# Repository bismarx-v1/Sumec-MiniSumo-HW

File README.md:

# SUMEC - HARDWARE - ELECTRONICS

**SUMEC** - is an autonomous MiniSumo robot, that is designed to compete in MiniSumo competitions. MiniSumo robots are small 100mmx100mm autonomous robots that combine electronics, software and mechanics into one project, their task it to push their opponent out of a ring. This project is led and managed by [SPŠ na Proseku](https://www.sps-prosek.cz) students.

## Table of Contents
- Description
- Contents
- Contributors
- Our Suppliers
- Contact
- Acknowledgements

## Description
This GitHub repository contains PCB files, gerber plots and main electronics used by SUMEC MiniSumo robot.

## Contents
- **main_hw**: Includes schematics and PCB files for the main board, production files such as Gerber plots and BOMs, .step files of the board, and PDF plots.
- **libs**: Contains needed libraries such as the footprint folder, 3D files in .step format, and the symbol library for schematics.

## Contributors
**HARDWARE Repository Supervisor**:
- **Savva Popov** - Head Hardware Developer and PCB Designer

**Project Contributors**:
- **Antonín Havlík** - Head Software Developer
- **Šimon Šťastný** - Head Mechanical Designer and Developer
- **Jonáš Jarý** - Mechanical Developer, Software and Hardware Development Assistant
- **Lukáš Houdek** - Mechanical Designer and Developer, 3D Printing Expert
- **Roselyn Natani Šimáčková** - Software developer, head functions developer

## Our Suppliers
We buy our components from:
- Mouser Electronics
- GM Electronics
- TME
- BotLand

## Contact
If you have any questions, suggestions, or issues regarding this project or repository, please feel free to contact:

### **Savva Popov** - Head Hardware Developer
  - Email: savva.popov.sp@gmail.com
  - LinkedIn: [Savva Popov](https://www.linkedin.com/in/savva-popov/)

### Other Contacts:
- **Antonín Havlík** - Head Software Developer
  - Email: [HAVLIK EMAIL]
- **Šimon Šťastný** - Head Mechanical Designer and Developer
  - Email: simon.ststn@gmail.com
- **Jonáš Jarý** - Mechanical Developer, Software and Hardware Development Assistant
  - Email: jary.jonas@gmail.com
- **Lukáš Houdek** - Mechanical Designer and Developer, 3D Printing Expert
  - Email: [HOUDEK EMAIL]
- **Roselyn Natani Šimáčková** - Software Developer, Head functions developer
  - Email: [SIMACKOVA EMAIL]

## Acknowledgements
We would like to thank Ing. Jaroslav Bušek PhD, for providing contacts and mentoring during the development of this project, and our school SPŠ na Proseku for providing workplace, knowledge, and top-notch equipment.

**Sending love from the Czech Republic!**

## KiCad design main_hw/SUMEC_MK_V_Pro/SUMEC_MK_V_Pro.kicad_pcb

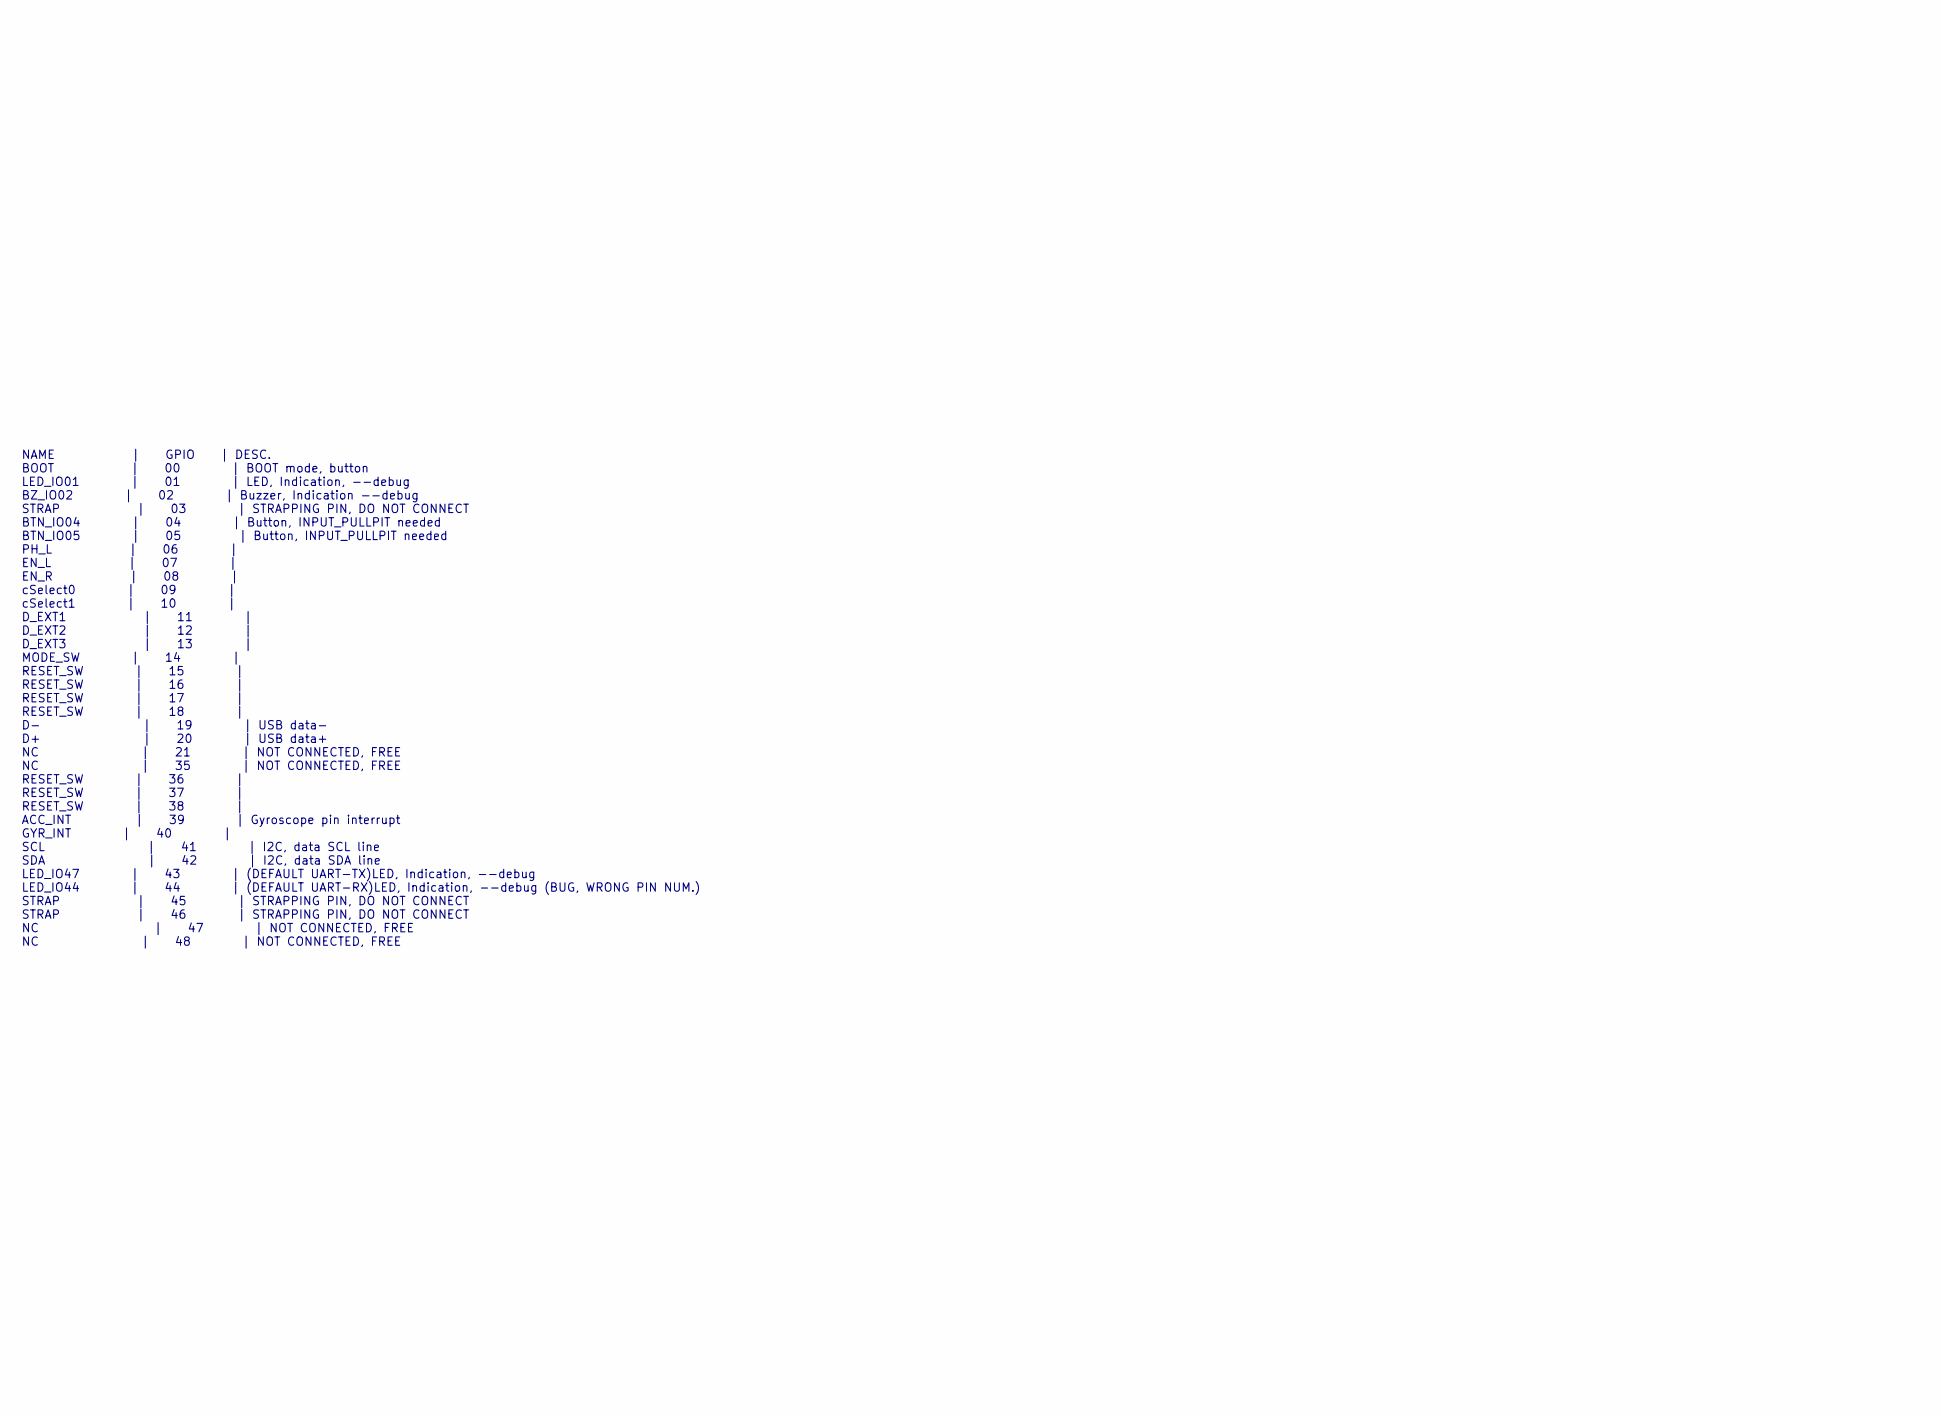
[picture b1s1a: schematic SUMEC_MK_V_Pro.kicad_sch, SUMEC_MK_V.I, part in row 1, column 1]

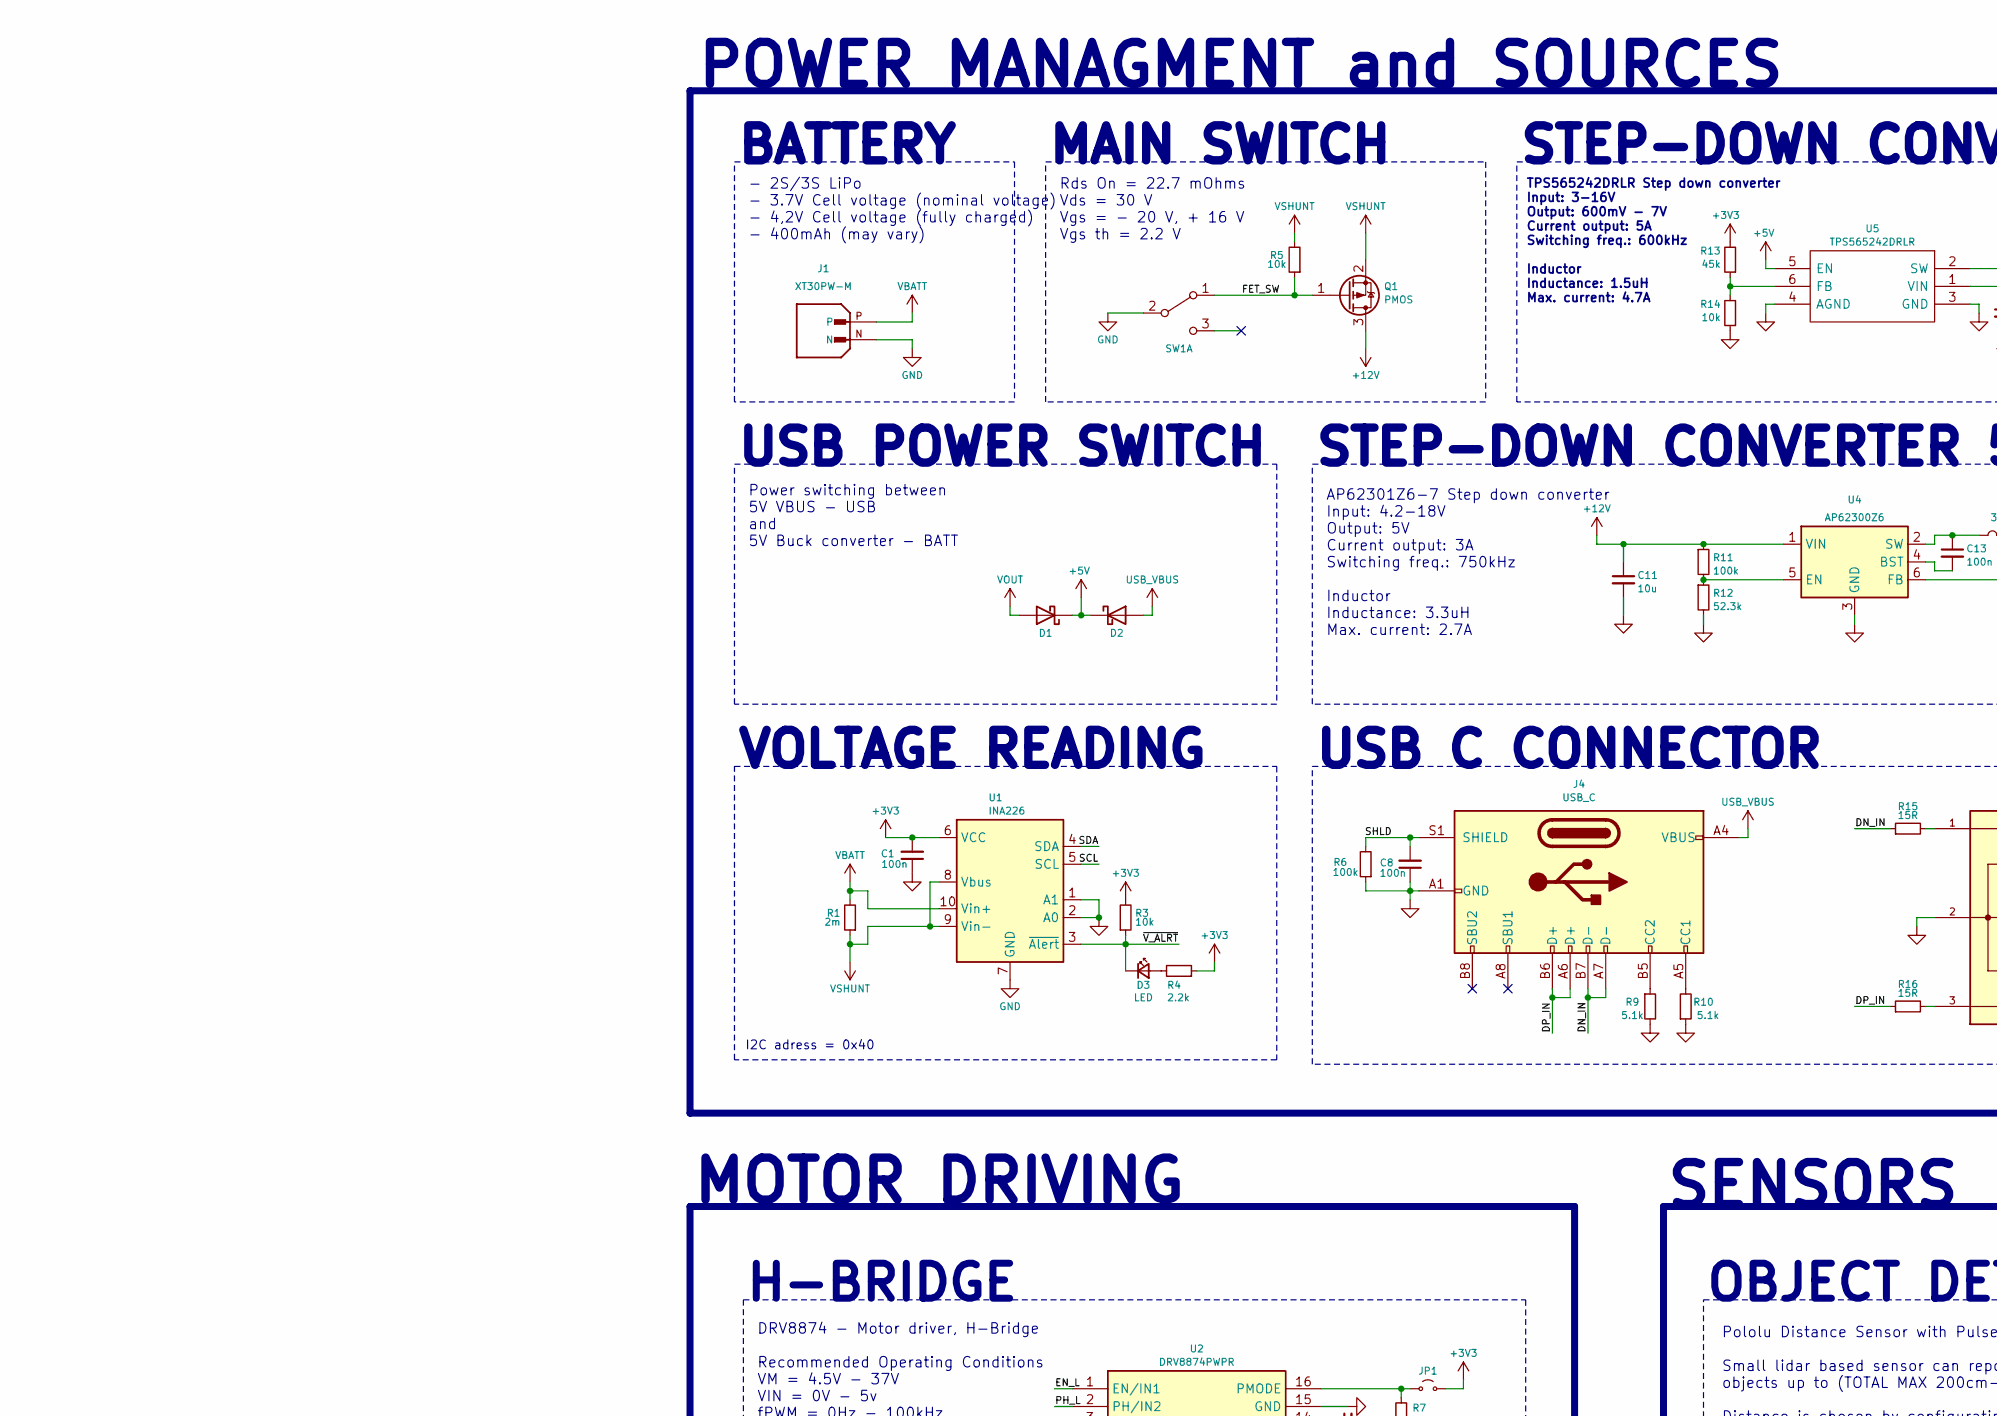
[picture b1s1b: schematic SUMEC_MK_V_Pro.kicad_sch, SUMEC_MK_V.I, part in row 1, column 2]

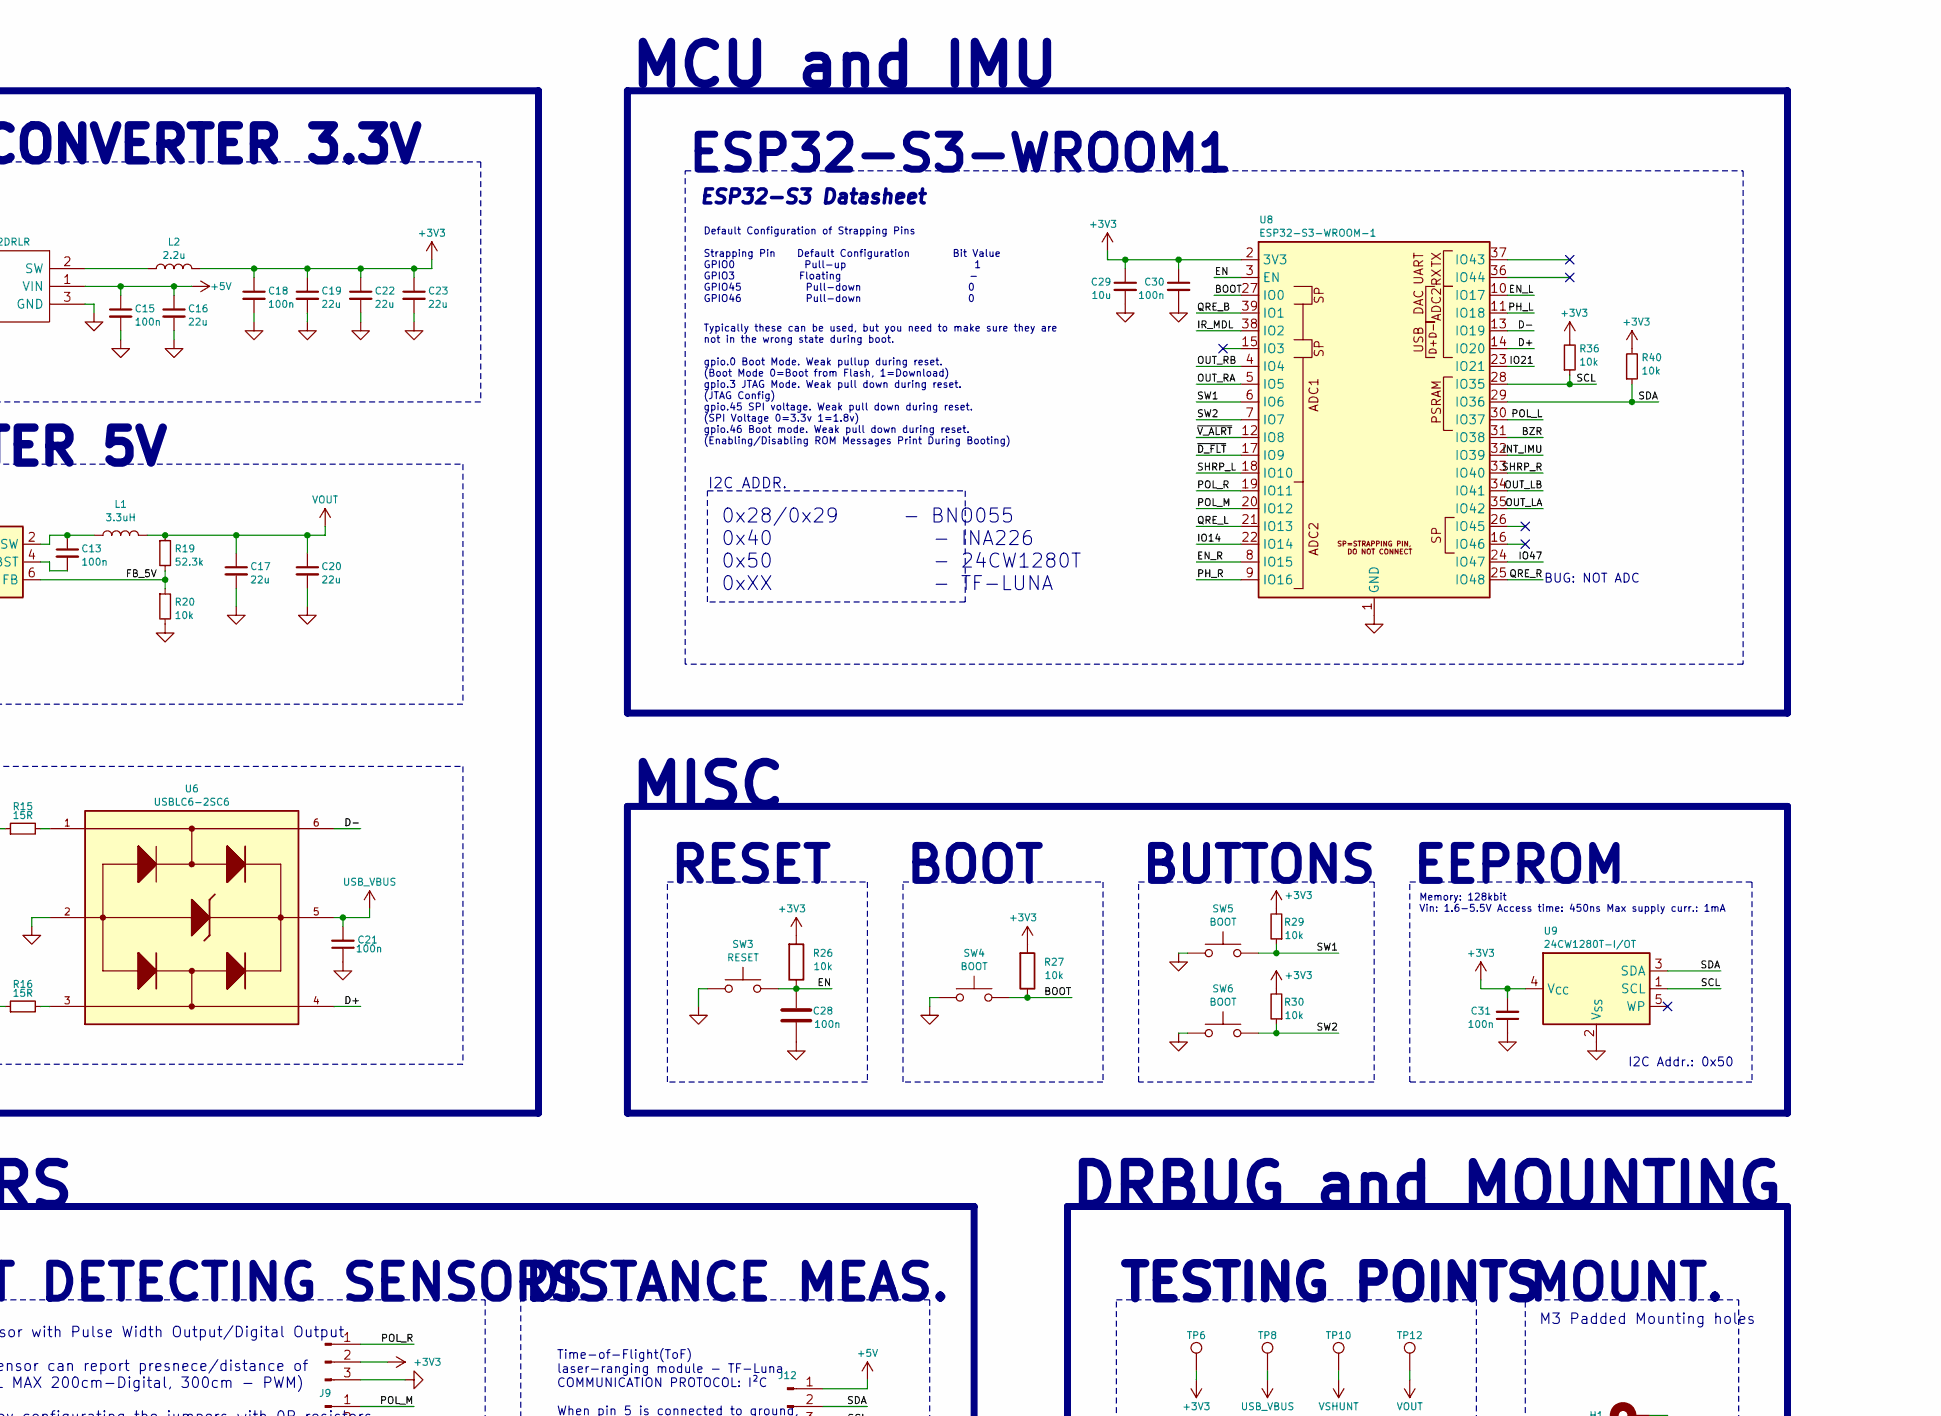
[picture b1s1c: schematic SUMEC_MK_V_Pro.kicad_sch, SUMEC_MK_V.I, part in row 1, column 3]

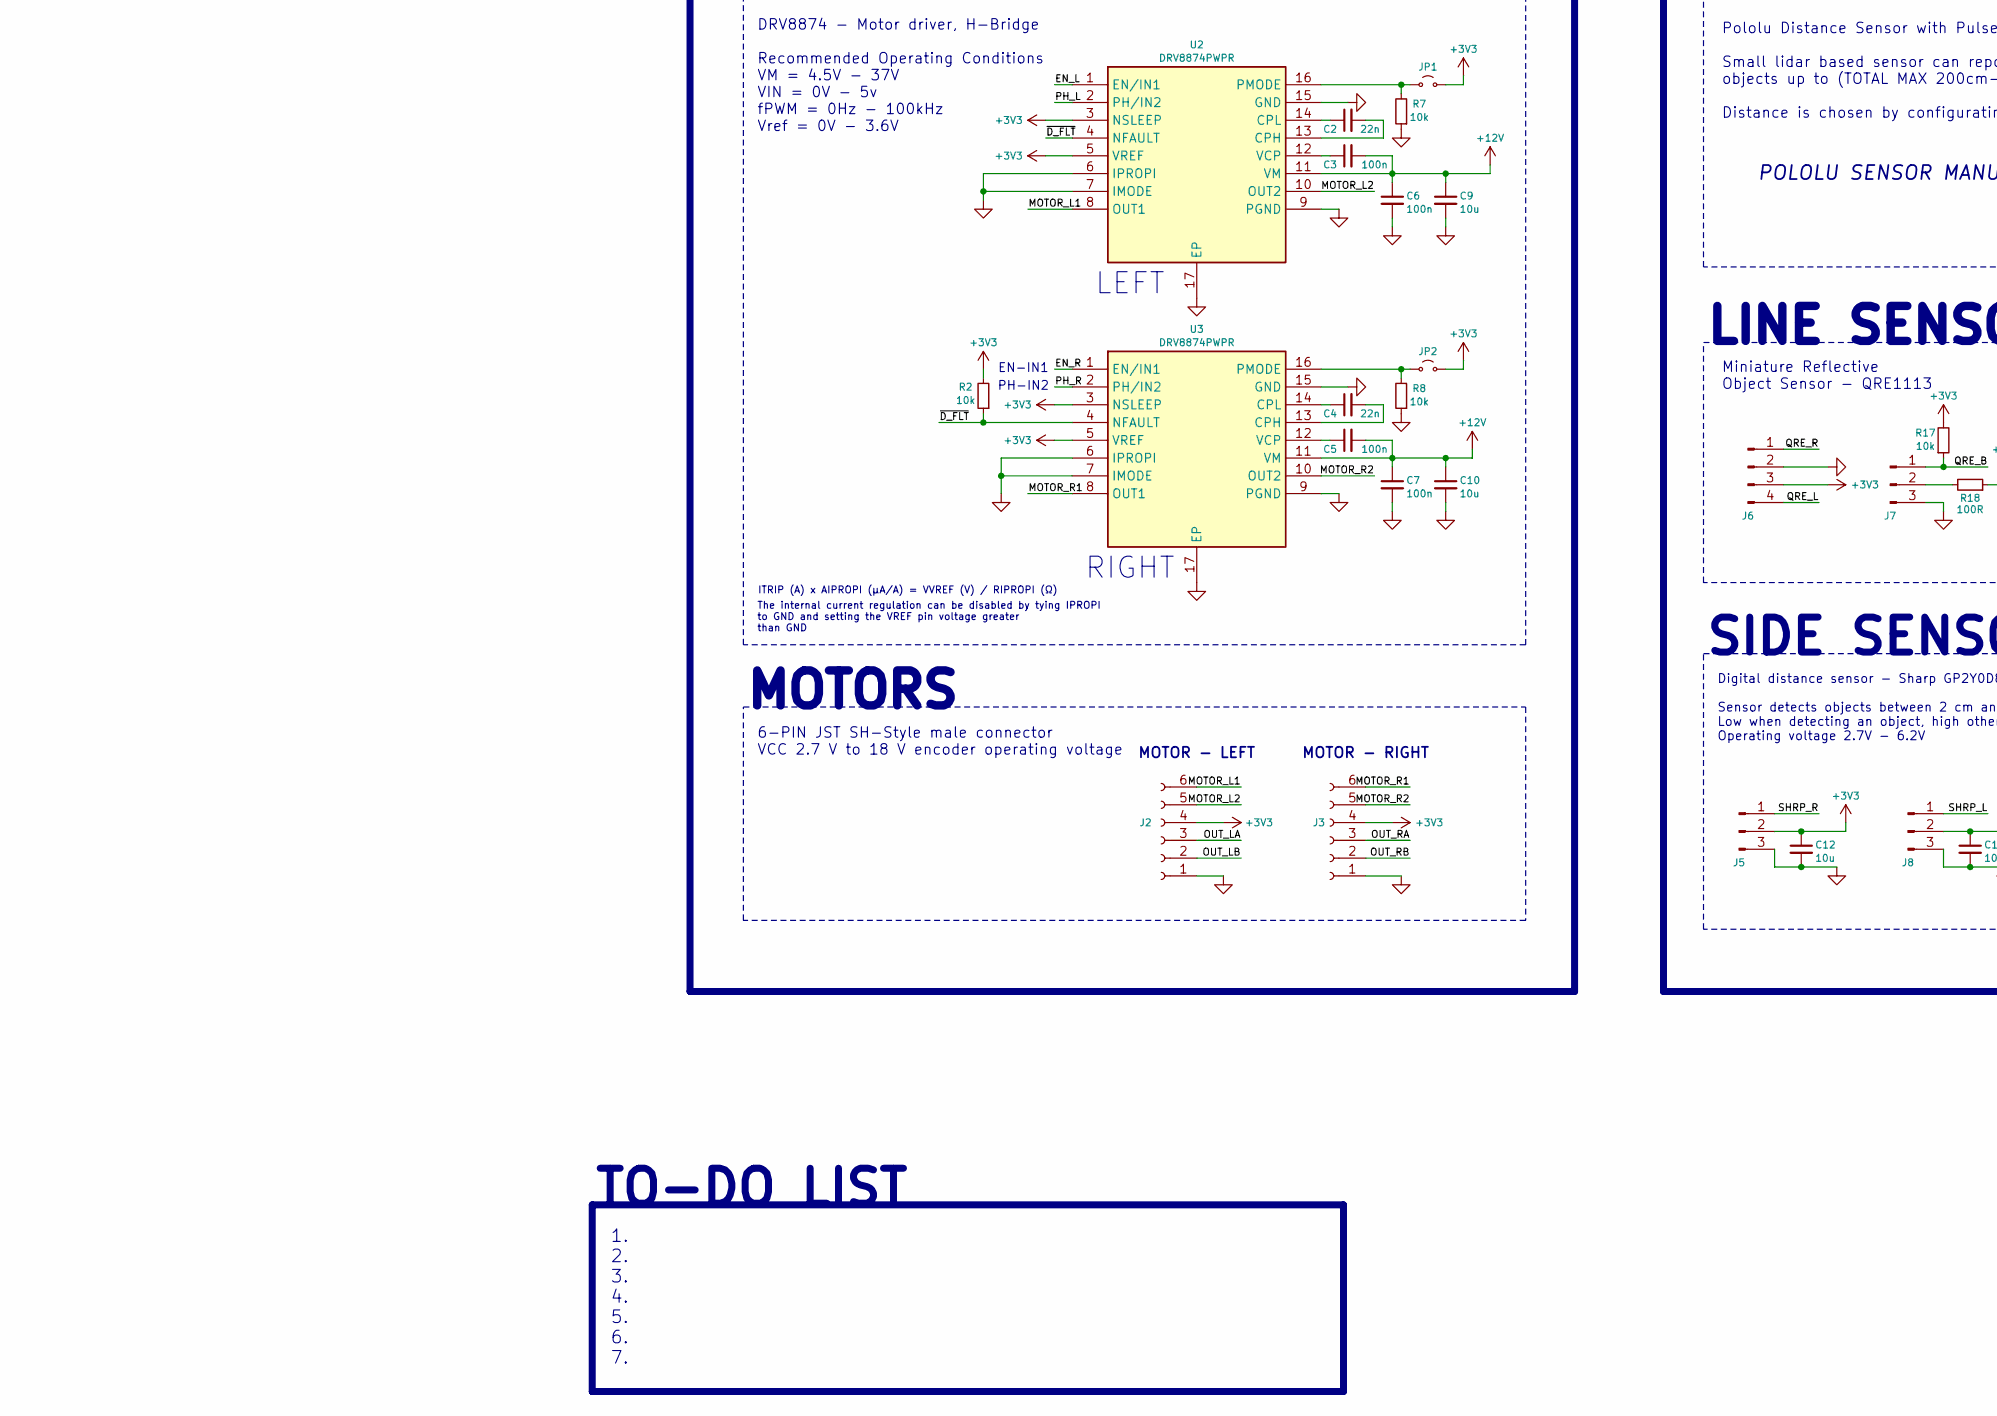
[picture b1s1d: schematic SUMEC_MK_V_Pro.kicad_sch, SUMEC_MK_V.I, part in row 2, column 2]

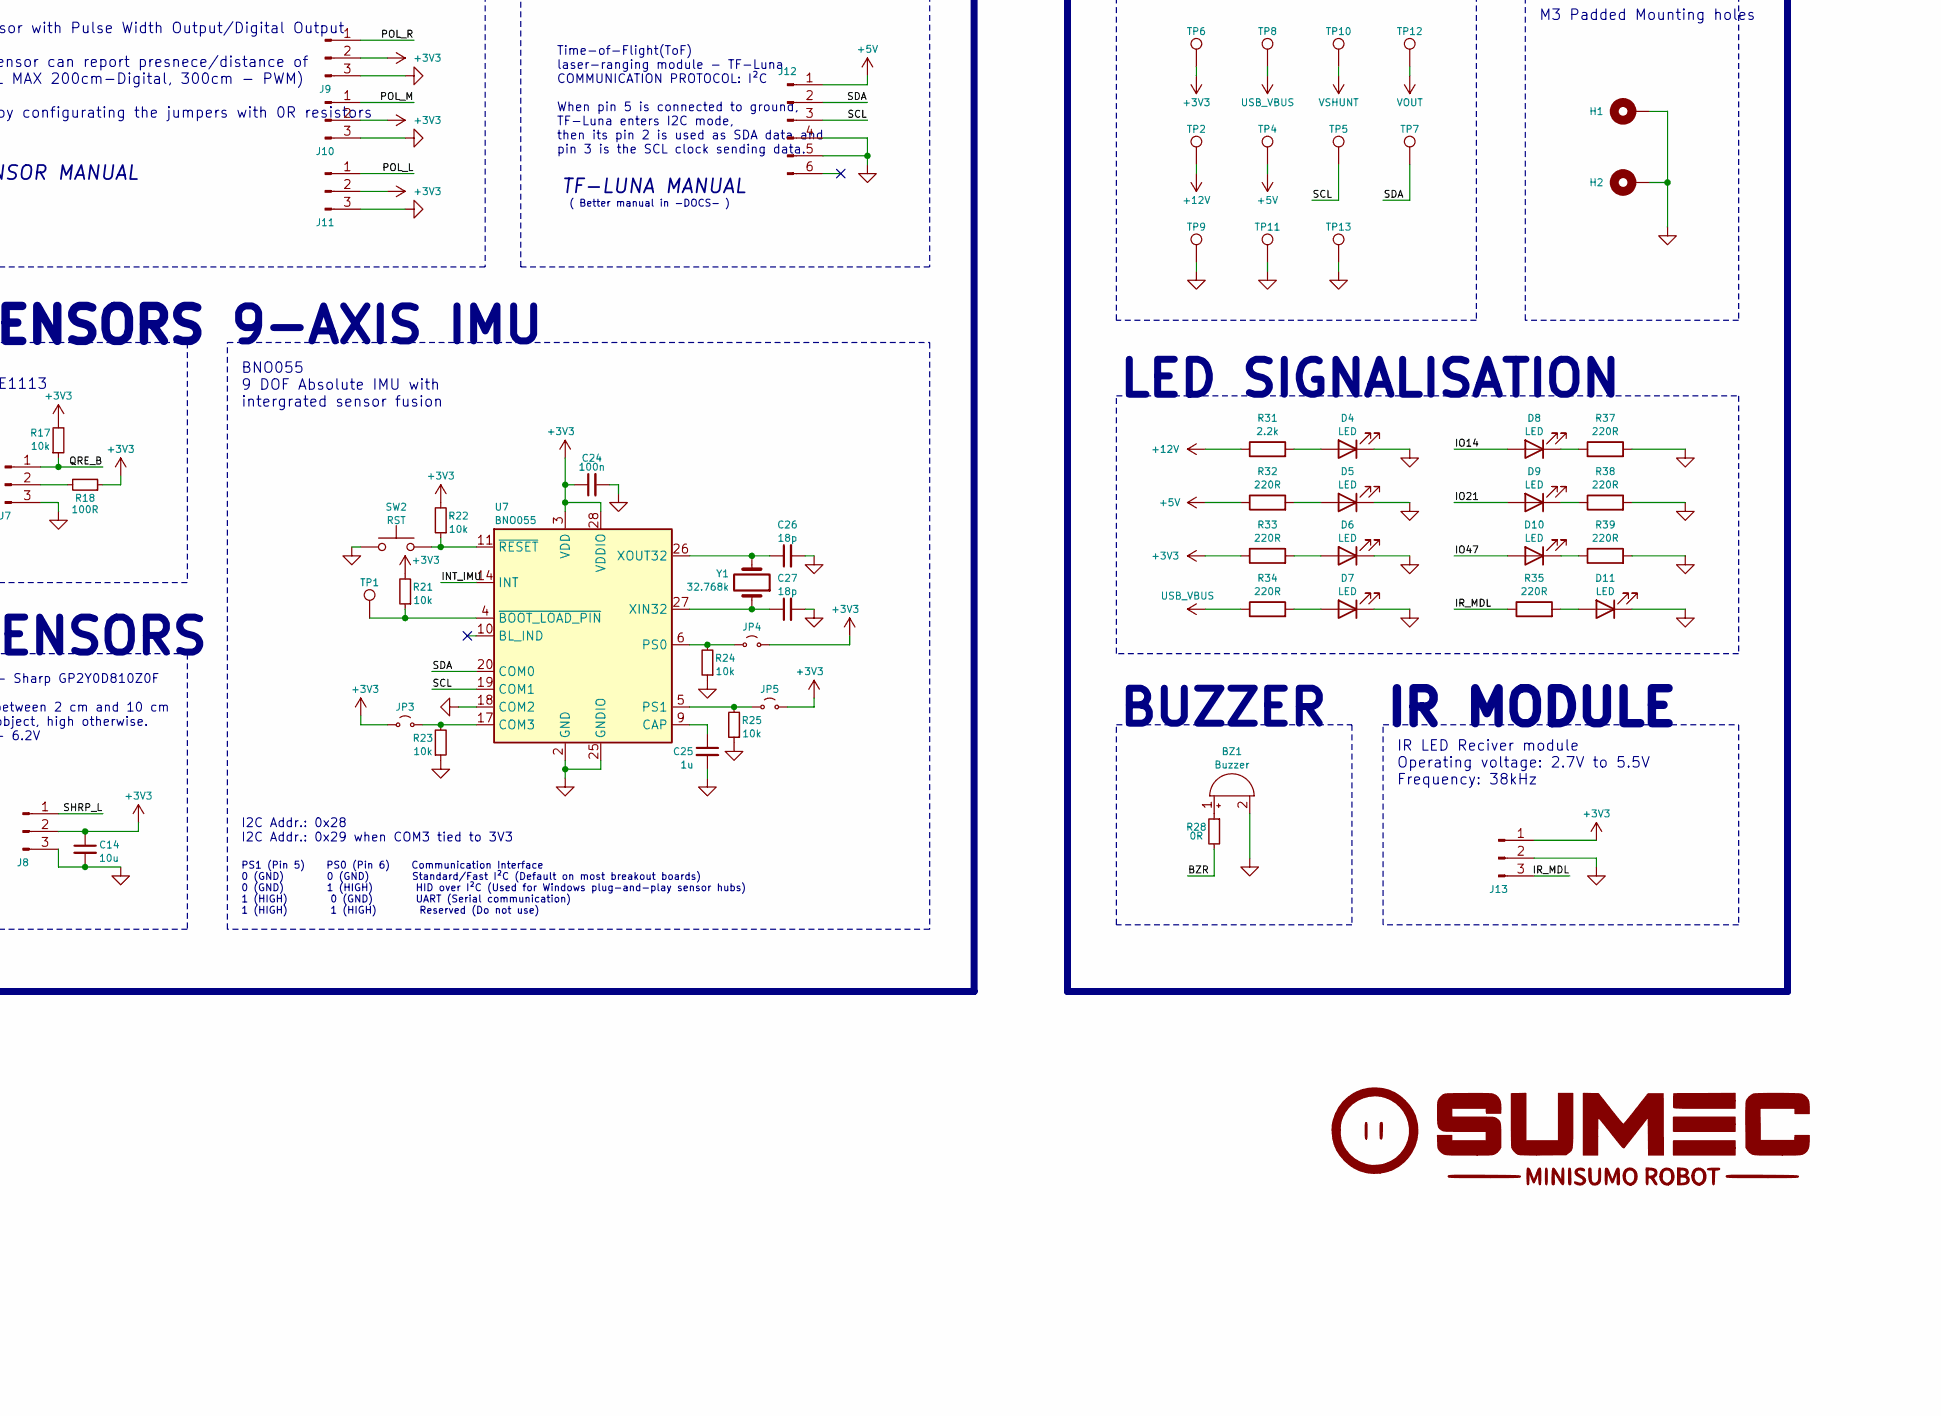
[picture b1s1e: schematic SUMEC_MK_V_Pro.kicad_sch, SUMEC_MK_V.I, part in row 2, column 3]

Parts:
BZ1: Buzzer; BUZZER_CUI_CPT
C1, C3, C5, C6, C7, C8, C13, C15, C18, C21, C24, C28, C30, C31: 100n; C_0805_2012Metric
C2, C4: 22n; C_0805_2012Metric
C9, C10, C11, C12, C14, C29: 10u; C_0805_2012Metric
C16, C17, C19, C20, C22, C23: 22u; C_0805_2012Metric
C25: 1u; C_0805_2012Metric
C26, C27: 18p; C_0805_2012Metric
D1, D2: D_Schottky; D_1206_3216Metric
D3, D4, D5, D6, D7, D8, D9, D10, D11: LED; LED_0805_2012Metric
H1, H2: Mounting Hole M3; MountingHole_3.2mm_M3_Pad_Via
J1: XT30PW-M; PARTREV 1.2
J2, J3: Conn_01x06_Socket; JST_SH_BM06B-SRSS-TB_1x06-1MP_P1.00mm_Vertical
J4: USB_C; USB_C_Receptacle_GCT_USB4105-xx-A_16P_TopMnt_Horizontal
J5, J7, J8, J9, J10, J11: Conn_01x03_Pin; Molex_PicoBlade_53398-0371_1x03-1MP_P1.25mm_Vertical
J6: Conn_01x04_Pin; Molex_PicoBlade_53398-0471_1x04-1MP_P1.25mm_Vertical
J12: Conn_01x06_Pin; Molex_PicoBlade_53398-0671_1x06-1MP_P1.25mm_Vertical
J13: Conn_01x03_Pin; TerminalBlock_Phoenix_MPT-0,5-3-2.54_1x03_P2.54mm_Horizontal
JP1, JP2, JP3, JP4, JP5: Jumper_2_Small_Open; SolderJumper-2_P1.3mm_Open_RoundedPad1.0x1.5mm
L1: 3.3uH; L_Vishay_IHLP-1616
L2: 2.2u; L_Vishay_IHLP-1212
Q1: PMOS; SOT-23-3
R1: 2m; R_0805_2012Metric
R2, R3, R5, R7, R8, R14, R17, R20, R21, R22, R23, R24, R25, R26, R27, R29, R30, R36, R40: 10k; R_0805_2012Metric
R4, R31: 2.2k; R_0805_2012Metric
R6, R11: 100k; R_0805_2012Metric
R9, R10: 5.1k; R_0805_2012Metric
R12, R19: 52.3k; R_0805_2012Metric
R13: 45k; R_0805_2012Metric
R15, R16: 15R; R_0805_2012Metric
R18: 100R; R_0805_2012Metric
R28: 0R; R_0805_2012Metric
R32, R33, R34, R35, R37, R38, R39: 220R; R_0805_2012Metric
SW1: SW_DPDT_x2; Custom_SPDT_2.5_Switch
SW2: RST; SW_SPST_EVQPE1
SW3: RESET; SW_SPST_EVQPE1
SW4, SW5, SW6: BOOT; SW_SPST_EVQPE1
TP1, TP2, TP4, TP5, TP6, TP7, TP8, TP9, TP10, TP11, TP12, TP13: TestPoint; TestPoint_Pad_D1.5mm
U1: INA226; HVSSOP-10-1EP_3x3mm_P0.5mm_EP1.83x1.89mm
U2, U3: DRV8874PWPR; DRV8874; Manufacturer_Part_Number DRV8874PWPR; Mouser Part Number 595-DRV8874PWPR
U4: AP62300Z6; SOT-563
U5: TPS565242DRLR; SOT-563; Manufacturer_Part_Number TPS565242DRLR; Mouser Part Number 595-TPS565242DRLR
U6: USBLC6-2SC6; TSOT-23-6
U7: BNO055; LGA-28_5.2x3.8mm_P0.5mm
U8: ESP32-S3-WROOM-1
U9: 24CW1280T-I/OT; SOT-23-5
Y1: 32.768k; CM8V32768TA020125

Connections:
+3V3: C1.2, C12.1, C14.1, C18.1, C19.1, C22.1, C23.1, C24.1, C29.1, C30.1, C31.2, J2.4, J3.4, J5.2, J6.3, J8.2, J9.2, J10.2, J11.2, J13.1, JP1.2 (B), JP2.2 (B), JP3.2 (B), JP4.2 (B), JP5.2 (B), L2.2, R2.2, R3.2, R4.1, R13.2, R17.2, R18.1, R21.2, R22.2, R26.2, R27.2, R29.2, R30.2, R33.1, R36.2, R40.2, TP6.1 (1_1), U1.6 (VCC), U2.3 (NSLEEP), U2.5 (VREF), U3.3 (NSLEEP), U3.5 (VREF), U7.3 (VDD), U7.28 (VDDIO), U8.2 (3V3), U9.4 (V_{CC})
+5V: C15.1, C16.1, D1.1 (K), D2.1 (K), J12.1, R32.1, TP4.1 (1_1), U5.1 (VIN), U5.5 (EN)
+12V: C3.2, C5.2, C6.1, C7.1, C9.1, C10.1, C11.1, Q1.3 (D), R11.1, R31.1, TP2.1 (1_1), U2.11 (VM), U3.11 (VM), U4.1 (VIN)
/BOOT: R27.1, SW4.2, U8.27 (IO0)
/BZR: R28.2, U8.31 (IO38)
/D+: U6.4, U8.14 (IO20)
/D-: U6.6, U8.13 (IO19)
/DN_IN: J4.A7 (D-), J4.B7 (D-), R15.1
/DP_IN: J4.A6 (D+), J4.B6 (D+), R16.1
/EN: C28.2, R26.1, SW3.2, U8.3 (EN)
/EN_L: U2.1 (EN/IN1), U8.10 (IO17)
/EN_R: U3.1 (EN/IN1), U8.8 (IO15)
/FB_5V: R19.2, R20.1, U4.6 (FB)
/FET_SW: Q1.1 (G), R5.1, SW1.1 (A)
/INT_IMU: U7.14 (INT), U8.32 (IO39)
/IO14: D8.2 (A), U8.22 (IO14)
/IO21: D9.2 (A), U8.23 (IO21)
/IO47: D10.2 (A), U8.24 (IO47)
/IR_MDL: J13.3, R35.1, U8.38 (IO2)
/MOTOR_L1: J2.6, U2.8 (OUT1)
/MOTOR_L2: J2.5, U2.10 (OUT2)
/MOTOR_R1: J3.6, U3.8 (OUT1)
/MOTOR_R2: J3.5, U3.10 (OUT2)
/OUT_LA: J2.3, U8.35 (IO42)
/OUT_LB: J2.2, U8.34 (IO41)
/OUT_RA: J3.3, U8.5 (IO5)
/OUT_RB: J3.2, U8.4 (IO4)
/PH_L: U2.2 (PH/IN2), U8.11 (IO18)
/PH_R: U3.2 (PH/IN2), U8.9 (IO16)
/POL_L: J11.1, U8.30 (IO37)
/POL_M: J10.1, U8.20 (IO12)
/POL_R: J9.1, U8.19 (IO11)
/QRE_B: J7.1, R17.1, U8.39 (IO1)
/QRE_L: J6.4, U8.21 (IO13)
/QRE_R: J6.1, U8.25 (IO48)
/SCL: J12.3, R36.1, TP5.1 (1_1), U1.5 (SCL), U7.19 (COM1), U8.28 (IO35), U9.1 (SCL)
/SDA: J12.2, R40.1, TP7.1 (1_1), U1.4 (SDA), U7.20 (COM0), U8.29 (IO36), U9.3 (SDA)
/SHLD: C8.2, J4.S1 (SHIELD), R6.2
/SHRP_L: J8.1, U8.18 (IO10)
/SHRP_R: J5.1, U8.33 (IO40)
/SW1: R29.1, SW5.2, U8.6 (IO6)
/SW2: R30.1, SW6.2, U8.7 (IO7)
/~D_FLT: R2.1, U2.4 (NFAULT), U3.4 (NFAULT), U8.17 (IO9)
/~V_ALRT: D3.1 (K), R3.1, U1.3 (~Alert), U8.12 (IO8)
GND: BZ1.2 (-), C1.1, C6.2, C7.2, C8.1, C9.2, C10.2, C11.2, C12.2, C14.2, C15.2, C16.2, C17.2, C18.2, C19.2, C20.2, C21.1, C22.2, C23.2, C24.2, C25.2, C26.2, C27.2, C28.1, C29.2, C30.2, C31.1, D4.1 (K), D5.1 (K), D6.1 (K), D7.1 (K), D11.1 (K), H1.1 (1_1), H2.1 (1_1), J1.N, J2.1, J3.1, J4.A1 (GND), J4.A12 (GND), J4.B1 (GND), J4.B12 (GND), J5.3, J6.2, J7.3, J8.3, J9.3, J10.3, J11.3, J12.4, J12.5, J13.2, R6.1, R7.1, R8.1, R9.2, R10.1, R12.2, R14.1, R20.2, R23.1, R24.1, R25.1, R37.2, R38.2, R39.2, SW1.2 (B), SW2.1, SW3.1, SW4.1, SW5.1, SW6.1, TP9.1 (1_1), TP11.1 (1_1), TP13.1 (1_1), U1.1 (A1), U1.2 (A0), U1.7 (GND), U2.6 (IPROPI), U2.7 (IMODE), U2.9 (PGND), U2.15 (GND), U2.17 (EP), U3.6 (IPROPI), U3.7 (IMODE), U3.9 (PGND), U3.15 (GND), U3.17 (EP), U4.3 (GND), U5.3 (GND), U5.4 (AGND), U6.2, U7.2 (GND), U7.18 (COM2), U7.25 (GNDIO), U8.1 (GND), U8.40 (GND), U8.41 (GND), U9.2 (V_{SS})
unnamed: BZ1.1 (+), R28.1
unnamed: D3.2 (A), R4.2
unnamed: D4.2 (A), R31.2
unnamed: D5.2 (A), R32.2
unnamed: D6.2 (A), R33.2
unnamed: D7.2 (A), R34.2
unnamed: D8.1 (K), R37.1
unnamed: D9.1 (K), R38.1
unnamed: D10.1 (K), R39.1
unnamed: D11.2 (A), R35.2
unnamed: J4.A5 (CC1), R10.2
unnamed: J4.B5 (CC2), R9.1
unnamed: J7.2, R18.2
unnamed: JP1.1 (A), R7.2, U2.16 (PMODE)
unnamed: JP2.1 (A), R8.2, U3.16 (PMODE)
unnamed: JP3.1 (A), R23.2, U7.17 (COM3)
unnamed: JP4.1 (A), R24.2, U7.6 (PS0)
unnamed: JP5.1 (A), R25.2, U7.5 (PS1)
unnamed: R15.2, U6.1
unnamed: R16.2, U6.3
unnamed: C2.2, U2.13 (CPH)
unnamed: C2.1, U2.14 (CPL)
unnamed: C3.1, U2.12 (VCP)
unnamed: C4.2, U3.13 (CPH)
unnamed: C4.1, U3.14 (CPL)
unnamed: C5.1, U3.12 (VCP)
unnamed: C13.2, U4.4 (BST)
unnamed: R11.2, R12.1, U4.5 (EN)
unnamed: C13.1, L1.1, U4.2 (SW)
unnamed: R13.1, R14.2, U5.6 (FB)
unnamed: L2.1, U5.2 (SW)
unnamed: C25.1, U7.9 (CAP)
unnamed: C27.1, U7.27 (XIN32), Y1.1
unnamed: C26.1, U7.26 (XOUT32), Y1.2
unnamed: R21.1, TP1.1 (1_1), U7.4 (~BOOT_LOAD_PIN)
unnamed: R22.1, SW2.2, U7.11 (~RESET)
USB_VBUS: C21.2, D2.2 (A), J4.A4 (VBUS), J4.A9 (VBUS), J4.B4 (VBUS), J4.B9 (VBUS), R34.1, TP8.1 (1_1), U6.5
VBATT: J1.P, R1.2, U1.10 (Vin+)
VOUT: C17.1, C20.1, D1.2 (A), L1.2, R19.1, TP12.1 (1_1)
VSHUNT: Q1.2 (S), R1.1, R5.2, TP10.1 (1_1), U1.8 (Vbus), U1.9 (Vin-)

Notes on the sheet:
Default Configuration of Strapping Pins Strapping Pin Default Configuration Bit Value GPIO0 Pull-up 1 GPIO3 Floating - GPIO45 Pull-down 0 GPIO46 Pull-down 0
IR LED Reciver module Operating voltage: 2.7V to 5.5V Frequency: 38kHz
M3 Padded Mounting holes
STEP-DOWN CONVERTER 5V
6-PIN JST SH-Style male connector VCC 2.7 V to 18 V encoder operating voltage
AP62301Z6-7 Step down converter Input: 4.2-18V Output: 5V Current output: 3A Switching freq.: 750kHz Inductor Inductance: 3.3uH Max. current: 2.7A
LEFT
BUZZER
0x28/0x29 - BNO055 0x40 - INA226 0x50 - 24CW1280T 0xXX - TF-LUNA
SENSORS
TF-LUNA MANUAL
I2C Addr.: 0x50
( Better manual in -DOCS- )
STEP-DOWN CONVERTER 3.3V
OBJECT DETECTING SENSORS
PS1 (Pin 5) PS0 (Pin 6) Communication Interface 0 (GND) 0 (GND) Standard/Fast I²C (Default on most breakout boards) 0 (GND) 1 (HIGH) HID over I²C (Used for Windows plug-and-play sensor hubs) 1 (HIGH) 0 (GND) UART (Serial communication) 1 (HIGH) 1 (HIGH) Reserved (Do not use)
Digital distance sensor - Sharp GP2Y0D810Z0F Sensor detects objects between 2 cm and 10 cm Low when detecting an object, high otherwise. Operating voltage 2.7V - 6.2V
MOTOR - RIGHT
TPS565242DRLR Step down converter Input: 3-16V Output: 600mV - 7V Current output: 5A Switching freq.: 600kHz Inductor Inductance: 1.5uH Max. current: 4.7A
I2C ADDR.
EEPROM
MOUNT.
BNO055 9 DOF Absolute IMU with intergrated sensor fusion
VOLTAGE READING
Rds On = 22.7 mOhms Vds = 30 V Vgs = - 20 V, + 16 V Vgs th = 2.2 V
NAME | GPIO | DESC. BOOT | 00 | BOOT mode, button LED_IO01 | 01 | LED, Indication, --debug BZ_IO02 | 02 | Buzzer, Indication --debug STRAP | 03 | STRAPPING PIN, DO NOT CONNECT BTN_IO04 | 04 | Button, INPUT_PULLPIT needed BTN_IO05 | 05 | Button, INPUT_PULLPIT needed PH_L | 06 | EN_L | 07 | EN_R | 08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
I2C Addr.: 0x28 I2C Addr.: 0x29 when COM3 tied to 3V3
MAIN SWITCH
MOTOR - LEFT
- 2S/3S LiPo - 3.7V Cell voltage (nominal voltage) - 4,2V Cell voltage (fully charged) - 400mAh (may vary)
DRBUG and MOUNTING
LED SIGNALISATION
Pololu Distance Sensor with Pulse Width Output/Digital Output Small lidar based sensor can report presnece/distance of objects up to (TOTAL MAX 200cm-Digital, 300cm - PWM) Distance is chosen by configurating the jumpers with 0R resistors
EN-IN1
ITRIP (A) x AIPROPI (μA/A) = VVREF (V) / RIPROPI (Ω)
MOTORS
9-AXIS IMU
TO-DO LIST
MISC
I2C adress = 0x40

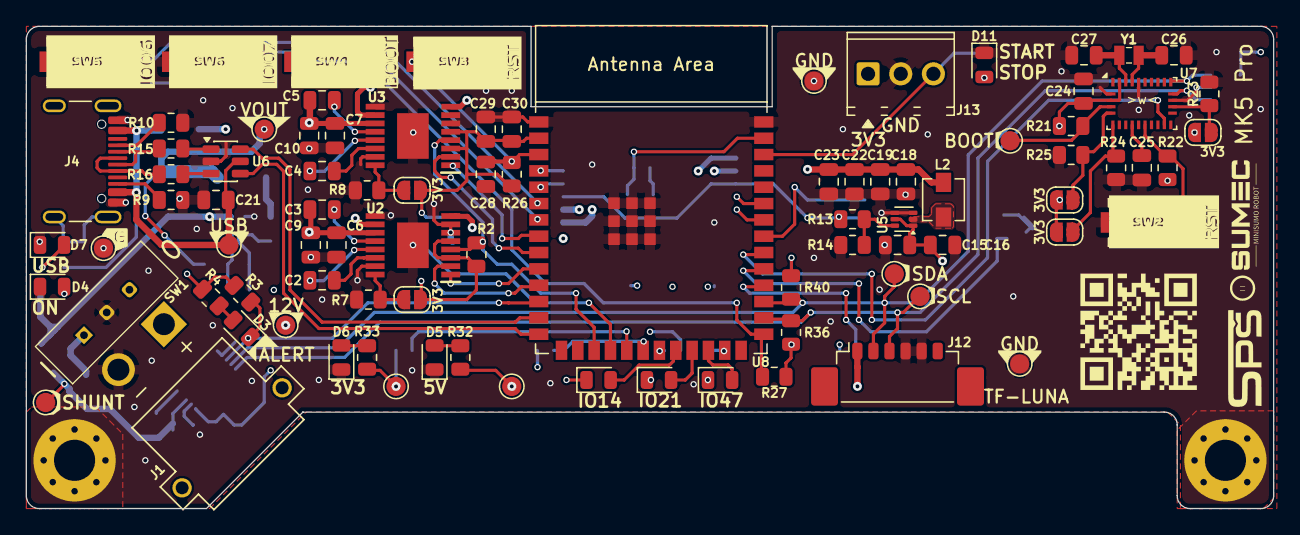
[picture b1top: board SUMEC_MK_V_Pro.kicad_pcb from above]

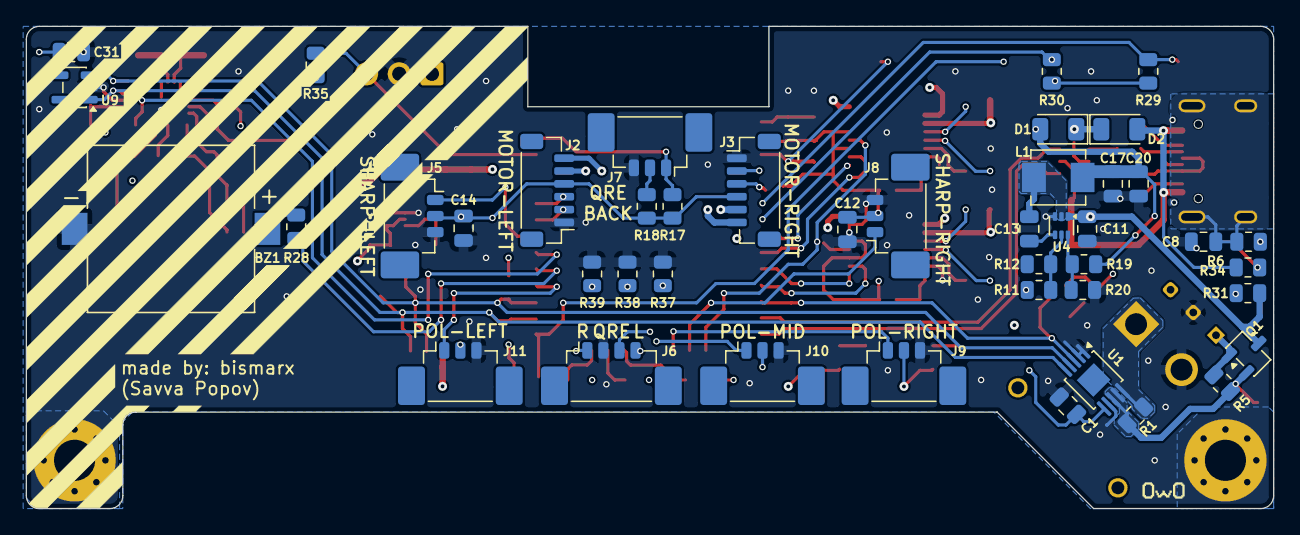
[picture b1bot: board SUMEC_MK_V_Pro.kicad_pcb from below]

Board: 4 copper layers, 97.0 x 37.5 mm, 137 parts (44 on the bottom side), 85 nets.

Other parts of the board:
TP1#2: TestPoint; SUMEC_QR_IMG
TP2#2: TestPoint; SPS_LOGO_IMG
TP3: TestPoint; SUMEC_LOGO_IMG

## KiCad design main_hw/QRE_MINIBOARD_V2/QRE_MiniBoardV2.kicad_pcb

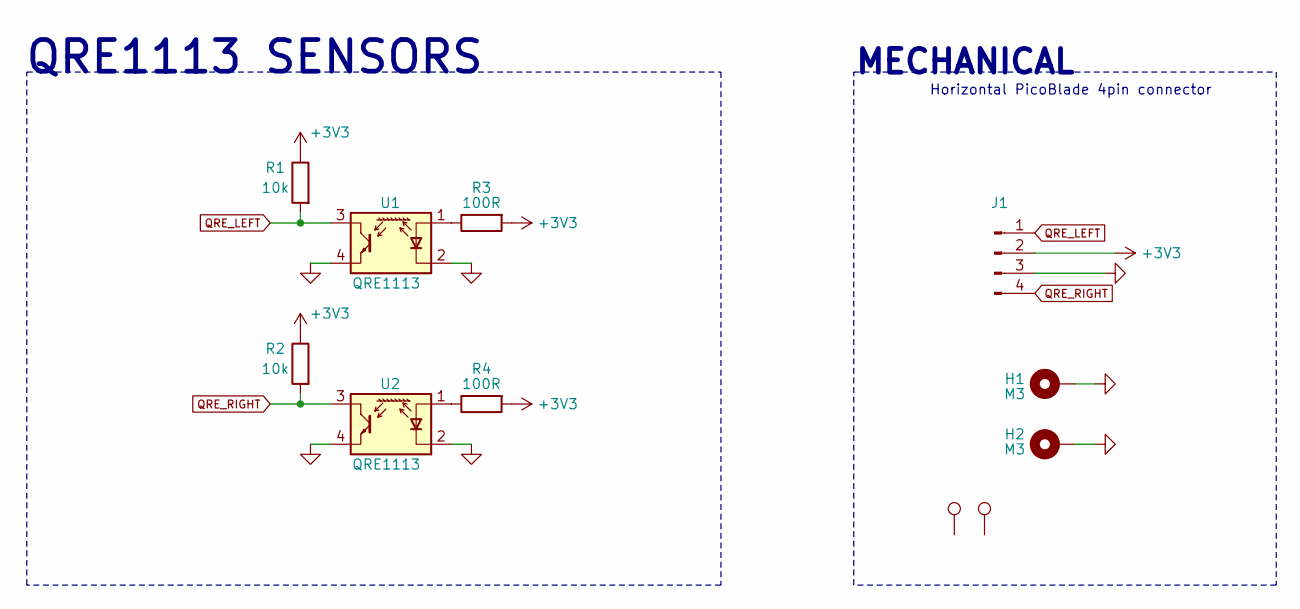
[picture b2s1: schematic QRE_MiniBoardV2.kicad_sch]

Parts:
H1, H2: M3; MountingHole_3.2mm_M3_Pad_Via
J1: Conn_01x04_Pin; Molex_PicoBlade_53261-0471_1x04-1MP_P1.25mm_Horizontal
R1, R2: 10k; R_0805_2012Metric_Pad1.20x1.40mm_HandSolder
R3, R4: 100R; R_0805_2012Metric_Pad1.20x1.40mm_HandSolder
TP1: TestPoint; BOYKISSER_IMG
TP2: TestPoint; OWO_IMG
U1, U2: QRE1113; OnSemi_CASE100CY

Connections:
+3V3: J1.2, R1.1, R2.1, R3.2, R4.2
GND: H1.1, H2.1, J1.3, U1.2 (K), U1.4, U2.2 (K), U2.4
unnamed: R3.1, U1.1 (A)
unnamed: R4.1, U2.1 (A)
QRE_LEFT: J1.1, R1.2, U1.3
QRE_RIGHT: J1.4, R2.2, U2.3

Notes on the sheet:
QRE1113 SENSORS
Horizontal PicoBlade 4pin connector
MECHANICAL
